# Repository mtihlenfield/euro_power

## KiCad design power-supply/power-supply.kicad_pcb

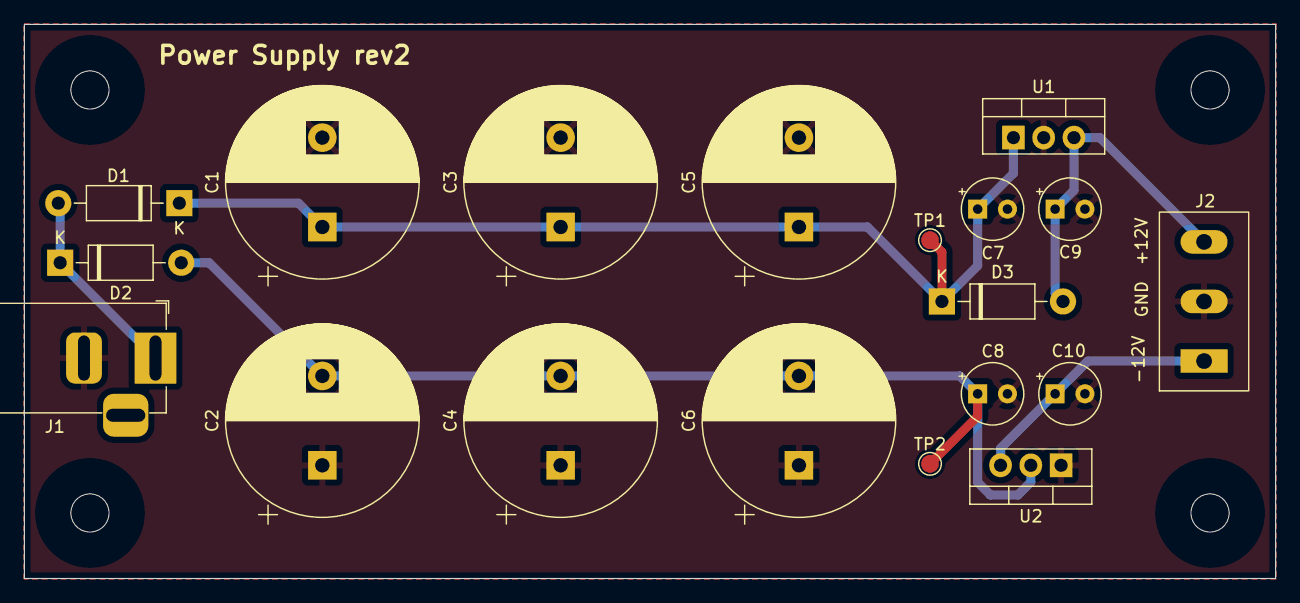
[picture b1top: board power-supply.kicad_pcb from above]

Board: 2 copper layers, 105.0 x 46.5 mm, 23 parts (0 on the bottom side), 6 nets.

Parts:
C1, C2, C3, C4, C5, C6: 4700uF; CP_Radial_D16.0mm_P7.50mm
C7: 0.33uF; CP_Radial_Tantal_D5.0mm_P2.50mm
C8: 2.2uF; CP_Radial_Tantal_D5.0mm_P2.50mm
C9: 0.1uF; CP_Radial_Tantal_D5.0mm_P2.50mm
C10: 1uF; CP_Radial_Tantal_D5.0mm_P2.50mm
D1, D2, D3: 1N4007; D_DO-41_SOD81_P10.16mm_Horizontal
H1, H2, H3, H4: MountingHole; MountingHole_3.2mm_M3
J1: Barrel_Jack_Switch; BarrelJack_Horizontal_2.1mm_WEALTH_METAL
J2: Output; DG126
TP1, TP2: TestPoint; TestPoint_Pad_D1.5mm
U1: LM7812_TO220; TO-220-3_Vertical
U2: LM7912_TO220; TO-220-3_Vertical

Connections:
GND: C1.2, C2.1, C3.2, C4.1, C5.2, C6.1, C7.2, C8.2, C9.2, C10.2, J1.2, J2.2, U1.2 (GND), U2.1 (GND)
unnamed: C1.1, C3.1, C5.1, C7.1, D1.1 (K), D3.1 (K), TP1.1, U1.1 (VI)
unnamed: C2.2, C4.2, C6.2, C8.1, D2.2 (A), TP2.1, U2.2 (VI)
unnamed: C9.1, D3.2 (A), J2.3, U1.3 (VO)
unnamed: C10.1, J2.1, U2.3 (VO)
unnamed: D1.2 (A), D2.1 (K), J1.1

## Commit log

2022-05-19 Added .gitignore
2022-05-19 .gitignore update
2022-05-19 Made mounting holes M3 sized. Generated BOM
2022-06-13 Updated for rev2
2022-07-23 Flipped input/output of 7912
2022-07-23 Added more text detail to PCB
